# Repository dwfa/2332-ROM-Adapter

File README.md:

Various Adpaters for the MOS 2332 ROM

In the **2732-TH** Directory is the PET 2332 to 2732 ROM Adapter

Overview

This repository contains the KiCad design files for an adapter board that allows a standard 2732 EPROM (Erasable Programmable Read-Only Memory) to function as a direct replacement for a MOS 2332 Mask ROM in vintage computer systems, specifically targeting Commodore PET computers (e.g., PET 8032, SuperPET).

The MOS 2332 is a 4KB (4096 x 8-bit) mask-programmable ROM often found in older systems. Due to their mask-programmed nature, these ROMs cannot be easily reprogrammed or replaced if faulty or if custom firmware is desired. This adapter board provides a modern, flexible solution by mapping the 2332's pinout and specific control logic to a readily available and reprogrammable 2732 EPROM.
Features

    * 2332 Pinout Adaptation: Correctly maps the address (A0-A11), data (D0-D7), and control signals of the 2332 ROM to the corresponding pins of a 2732 EPROM.
    * NOROM Signal Handling: Incorporates necessary 74LS series logic gates (74LS04 Hex Inverter and 74LS32 Quad 2-input OR Gate) to correctly interpret the PET system's NOROM signal, ensuring proper
      ROM enabling/disabling for normal operation and diagnostic purposes.
    * 2-Layer PCB: Designed as a cost-effective 2-layer printed circuit board, suitable for fabrication by most hobbyist-friendly PCB manufacturers.
    * Physical Compatibility:
        * 2332 Side: Utilizes through-hole pads for soldering standard 2x12 pin headers, allowing the adapter to plug directly into the existing 2332 ROM socket on the mainboard.
        * 2732 Side: Features a 24-pin DIP socket for easy insertion and replacement of a 2732 EPROM.
    * Robust Design Rules: Implements conservative design rules for trace width, clearance, via size, and solder mask, ensuring high manufacturability and reliability.

Compatibility

This adapter is designed to replace 2332 ROMs in systems that utilize the pinout and NOROM logic of the MOS 2332, such as the Commodore PET 8032 and SuperPET.
Getting Started (Building Your Own)

To build this adapter, you will need to:

    * Obtain the PCB:
        * Download the latest Gerber files from the Releases section of this repository.
        * Order the PCB from your preferred manufacturer (e.g., PCBWay, JLCPCB) using these Gerber files.
    * Gather Components: Refer to the Bill of Materials (BOM) section for the required components.
    * Assemble the Board: Solder the components onto the PCB according to the silkscreen markings and
      component placement.
    * Program Your 2732 EPROM: Load your desired 4KB (2048 x 16-bit or 4096 x 8-bit) ROM image into a
      2732 EPROM using an appropriate EPROM programmer.
    * Install: Plug the assembled adapter into the 2332 ROM socket on your target system.

Design Details
KiCad Version

    * Designed using KiCad 8.0.x. While efforts are made to ensure compatibility, older or newer KiCad
      versions may display minor differences.

Key Components

    * 2332 (Header): Connection points for 2x12 pin headers, 0.1" pitch, 0.6" row spacing (custom footprint).
    * 2732 (Socket): 24-pin DIP socket (0.6" wide).
    * 74LS04: 74LS04 Hex Inverter (14-pin DIP).
    * 74LS32: 74LS32 Quad 2-input OR Gate (14-pin DIP).

Layout Strategy

    * 2332 Interface: Utilizes through-hole pads on the top layer for soldering pin headers, with pins facing downwards.
    * 2732 Socket: Located on the top layer, soldered from the bottom.
    * Logic Gates: Placed on the top layer.
    * Routing: Achieved on a 2-layer board using a combination of top and bottom traces, with vias strategically placed to connect layers, manage
      signal remapping, and avoid trace crossings.
    * NOROM Logic Implementation: The adapter routes the relevant 2332 control signals (CS1, CS2) through the 74LS04 and 74LS32 gates to correctly
      drive the 2732's Chip Enable (overlineCE) pin. Unused inputs on the 74LS chips are tied directly to GND for stability.
    * Unused 74LS inputs are tied to ground

Bill of Materials (BOM)

| Designator | Qty | Part                                    | Footprint (KiCad)        | Description                       |
| :--------- | :-: | :-------------------------------------- | :----------------------- | :-------------------------------- |
| 2332       |  1  | 24-pin Pin Header (male)                 | PinHeader_2x12_DIP24_W15.24mm (custom) | To plug into 2332 socket        |
| 2732       |  1  | 24-pin DIP Socket                        | DIP-24_W15.24mm        | For 2732 EPROM                    |
| 74LS04     |  1  | 74LS04 Hex Inverter (14-pin DIP)         | DIP-14_W7.62mm         | Logic for NOROM                   |
| 74LS32     |  1  | 74LS32 Quad 2-input OR Gate (14-pin DIP) | DIP-14_W7.62mm         | Logic for NOROM                   |

License
This project is released under the GPL v3.0 License.

Acknowledgments

    The KiCad EDA Suite for excellent open-source PCB design tools.
    The vintage computing community for inspiring such projects.

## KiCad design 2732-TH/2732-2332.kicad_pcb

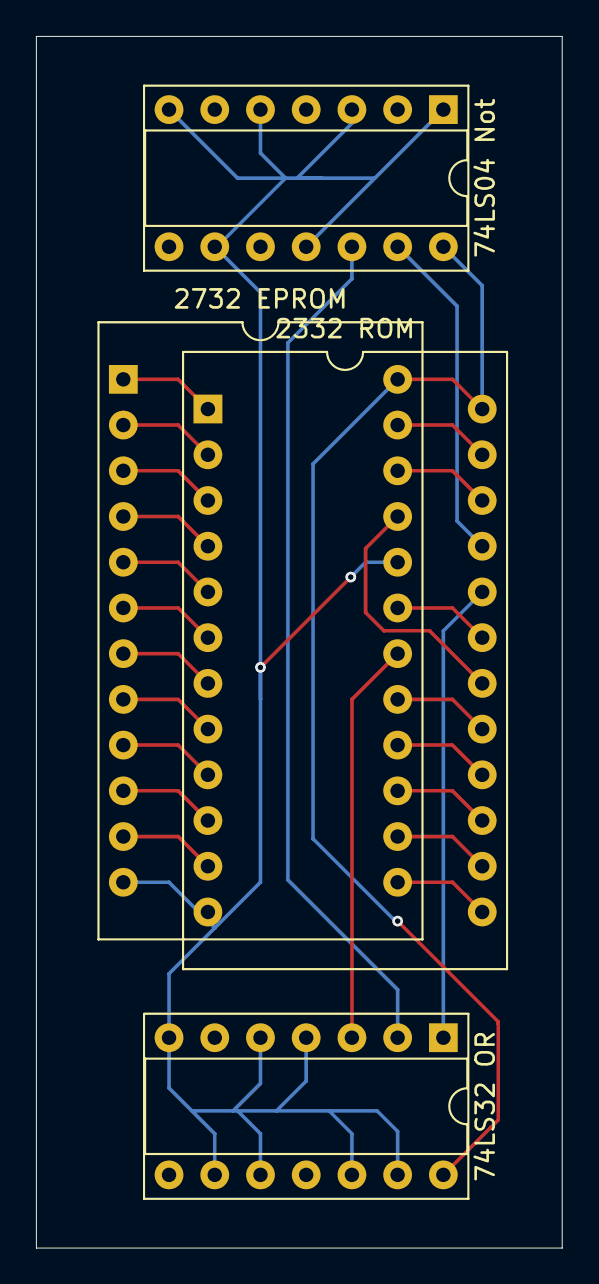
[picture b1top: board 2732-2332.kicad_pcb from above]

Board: 2 copper layers, 29.2 x 67.3 mm, 4 parts (0 on the bottom side), 26 nets.

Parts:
74LS04 Not, 74LS32 OR: DIP-14_Socket; DIP-14_W7.62mm_Socket
2332 ROM, 2732 EPROM: DIP-24_Socket; DIP-24_18.0mmx34.29mm_W15.24mm_Socket

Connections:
A0: 2332 ROM.8, 2732 EPROM.8
A1: 2332 ROM.7, 2732 EPROM.7
A2: 2332 ROM.6, 2732 EPROM.6
A3: 2332 ROM.5, 2732 EPROM.5
A4: 2332 ROM.4, 2732 EPROM.4
A5: 2332 ROM.3, 2732 EPROM.3
A6: 2332 ROM.2, 2732 EPROM.2
A7: 2332 ROM.1, 2732 EPROM.1
A8: 2332 ROM.23, 2732 EPROM.23
A9: 2332 ROM.22, 2732 EPROM.22
A10: 2332 ROM.19, 2732 EPROM.19
A11: 2332 ROM.18, 2732 EPROM.21
D0: 2332 ROM.9, 2732 EPROM.9
D1: 2332 ROM.10, 2732 EPROM.10
D2: 2332 ROM.11, 2732 EPROM.11
D3: 2332 ROM.13, 2732 EPROM.13
D4: 2332 ROM.14, 2732 EPROM.14
D5: 2332 ROM.15, 2732 EPROM.15
D6: 2332 ROM.16, 2732 EPROM.16
D7: 2332 ROM.17, 2732 EPROM.17
Ground: 74LS04 Not.1, 74LS04 Not.3, 74LS04 Not.5, 74LS04 Not.7, 74LS04 Not.9, 74LS04 Not.11, 74LS32 OR.4, 74LS32 OR.5, 74LS32 OR.7, 74LS32 OR.9, 74LS32 OR.10, 74LS32 OR.12, 74LS32 OR.13, 2332 ROM.12, 2732 EPROM.12, 2732 EPROM.20
Vcc: 74LS04 Not.14, 74LS32 OR.14, 2332 ROM.24, 2732 EPROM.24
notInput: 74LS04 Not.13, 2332 ROM.21
orInput1: 74LS32 OR.1, 2332 ROM.20
orInput2: 74LS04 Not.12, 74LS32 OR.2
orOutput: 74LS32 OR.3, 2732 EPROM.18
